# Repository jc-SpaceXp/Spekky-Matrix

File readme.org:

** Spekky Matrix
A FreeRTOS based project were a spectrum analyser is displayed on a LED matrix board run from a STM32 device
*** Detailed Description
A series of cascaded STP16CP05 LED IC drivers forms a 8x32 SMD (0603 Imperial)
LED matrix. This LED matrix then displays the fast fourier transform (FFT) of
an incoming audio signal picked up by a I2S digital microphone. The incoming
audio is a double buffered DMA signal. The LED matrix is driven via the
STM32's SPI interface. All while internal hardware timers and FreeRTOS are
responsible for accurate timing e.g. refresh rate of LED matrix and data
acquisition.

The Manhattan prototype uses a MAX7219 based 8x8 LED matrix breakout board
which was then cascaded to for a 8x32 LED matrix as well. In the PCB version
the STP16CP05 LED IC driver replaces the MAX7219 8x8 LED matrix.
*** Tools
The following tools are needed to build this project
- make
- [[https://developer.arm.com/downloads/-/gnu-rm][arm-none-eabi-gcc]]
- [[https://gcc.gnu.org/][gcc]] (for unit tests)
- [[https://github.com/stlink-org/stlink][st-flash]] in order to interact with the STM32
*** Progress / Milestones
- [X] Create LED matrix driver for MAX7219 devices
- [X] Drive LED matrix from STM32 using FreeRTOS
- [X] Run FFT off target
- [X] Verify FFT on target (using off target results as a guide)
- [X] Verify that LED matrix can be driven alongside FFT code (manually verified, no delays etc.)
- [X] Capture data from mic
- [X] Verify output of mic from raw logic analyser data (using SigPlotI2S)
- [X] Capture data from mic via DMA
- [X] Perform FFT on this raw logic analyser data with a sine wave test tone (off-target)
- [X] Animate FFT graphs to get a rough estimate of how the LED matrix will display it (off-target)
- [X] Perform FFT on mic data sampled by STM32 with a sine wave test tone (off-target)
- [X] Verify that LED matrix can be driven along with data capture and processing
- [X] Perform FFT on captured mic data to drive LED matrix
- [X] Adapt project to PCB
*** I2S Mic FFT Data Visualised
**** Logic Analyser Data (Sine 1kHz Test Tone)
FFT size = 64, start offset = 0, next offset = 32, FPS = 4

[[file:media/python_fft_logic_analyser_sine_1k.gif]]
**** Spekky Matrix Calculations
FFT size = 64, bin resolution = (1/60E-6)/64 --> ~260Hz

Note: I measured one Ws period as 60us on PulseView hence the 1/60E-6 above
***** 8x32 LED Matrix (Sine 2kHz Test Tone)
Peak expected at the 7th/8th bin (2000 / 260 = ~7.69)

[[file:media/blackman_harris_sine_2k.gif]]
***** 8x32 LED Matrix (Sine 4kHz Test Tone)
Peak expected at the 15th/16th bin (4000 / 260 = ~15.36)

[[file:media/blackman_harris_sine_4k.gif]]
***** 8x32 LED Matrix (Sine Sweep Test)
Since the I2S Ws period is 60us, this gives us a sampling frequency of 16.66 kHz.
 Giving us a visual representation of 0-8.88 kHz with Spekky Matrix

[[https://www.youtube.com/watch?v=dU80Fagdy28][Sine sweep source (youtube link)]]

Note: Gif is played at 2.5x speed, see mp4 for realtime playback and audio of sweep test

[[file:media/blackman_harris_sine_sweep.gif]]
*** Schematic
[[file:schematic_v26.pdf]]
*** KiCad PCB
**** BOM
[[file:pcb/kicad/spekky_matrix_bom.csv]]
**** 3D Renders
[[file:pcb/kicad/pcb_3d_front.png]]
[[file:pcb/kicad/pcb_3d_back.png]]
**** PCB v01 Test Patterns
Only displaying test patterns on PCB as v01 has the I2S footprint in the wrong orientation.

Attempted fix hasn't worked, PCB revision v04 contains fixed I2S footprint and test points.
[[file:media/pcb_v01_test_pattern_01.jpg]]
[[file:media/pcb_v01_test_pattern_02.jpg]]
*** Execution Timeline
Rough timing of how long each task/sub-task takes to complete

Actual times are a mean of the traces from the timing branch
[[file:execution_timeline.jpg]]
*** Submodules
- [[https://www.freertos.org/][FreeRTOS]]
- [[https://www.arm.com/technologies/cmsis][CMSIS V6]]
- [[https://github.com/ARM-software/CMSIS-DSP][ARM CMSIS DSP]]
- [[https://github.com/STMicroelectronics/stm32g4xx-nucleo-bsp][STM32G4xx Nucleo BSP]]
- [[https://github.com/STMicroelectronics/stm32g4xx_hal_driver][STM32G4 HAL]]
- [[https://github.com/STMicroelectronics/cmsis_device_g4][CMSIS G4]] CMSIS device library
- [[https://github.com/silentbicycle/greatest][Greatest]] C test framework
- [[https://github.com/meekrosoft/fff][fff]] C test doubles
- [[https://github.com/lucasssvaz/SigPlotI2S][SigPlotI2S]] Plot I2S PulseView/Sigrok output data

CMSIS will also produce linker warnings due to newlib e.g. "_write is not
implemented and will always fail". There is quite a bit of a size overhead
when pulling in all the CMSIS modules. An average project would be
around ~100Mb. This increases with FreeRTOS too.

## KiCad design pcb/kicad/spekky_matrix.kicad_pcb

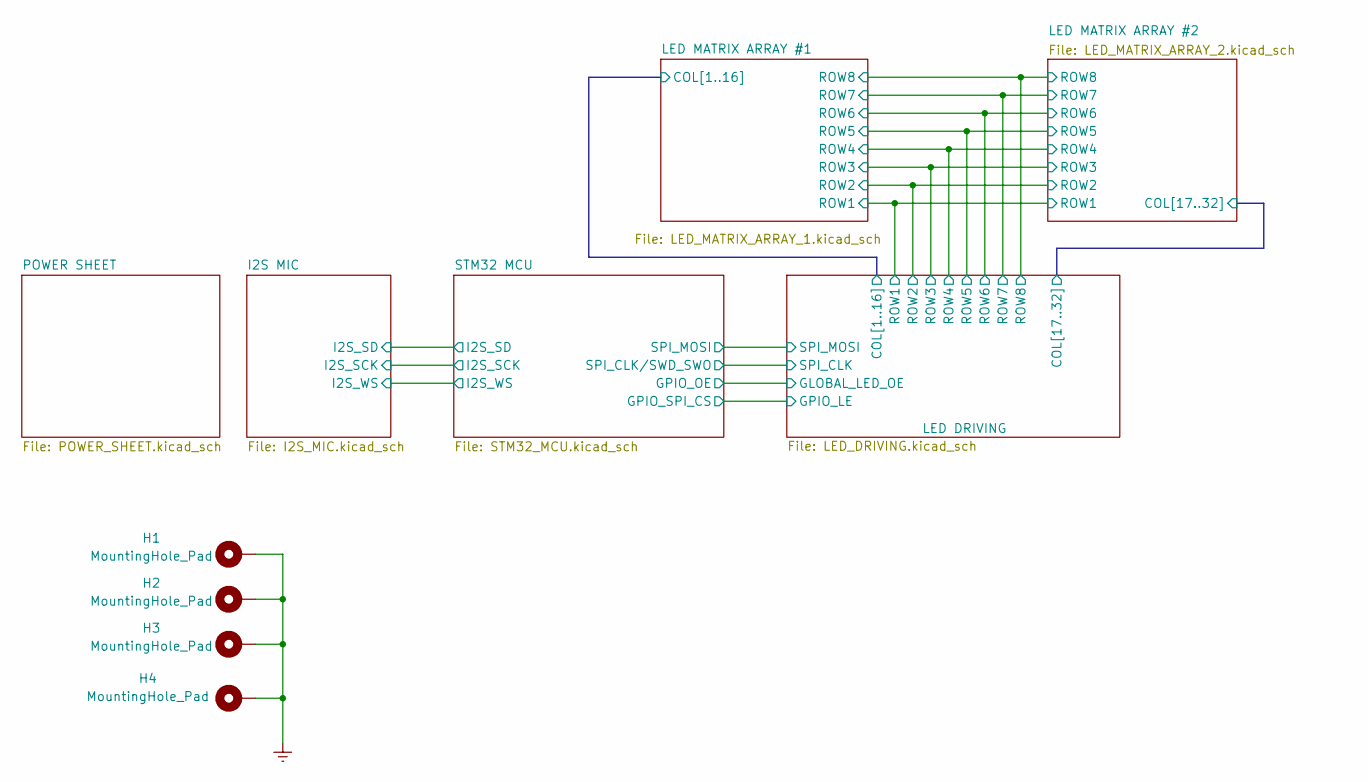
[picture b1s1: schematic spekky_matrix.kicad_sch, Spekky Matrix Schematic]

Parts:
H1, H2, H3, H4: MountingHole_Pad; MountingHole_3.2mm_M3_Pad

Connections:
GND: H1.1, H2.1, H3.1, H4.1; also elsewhere on the board

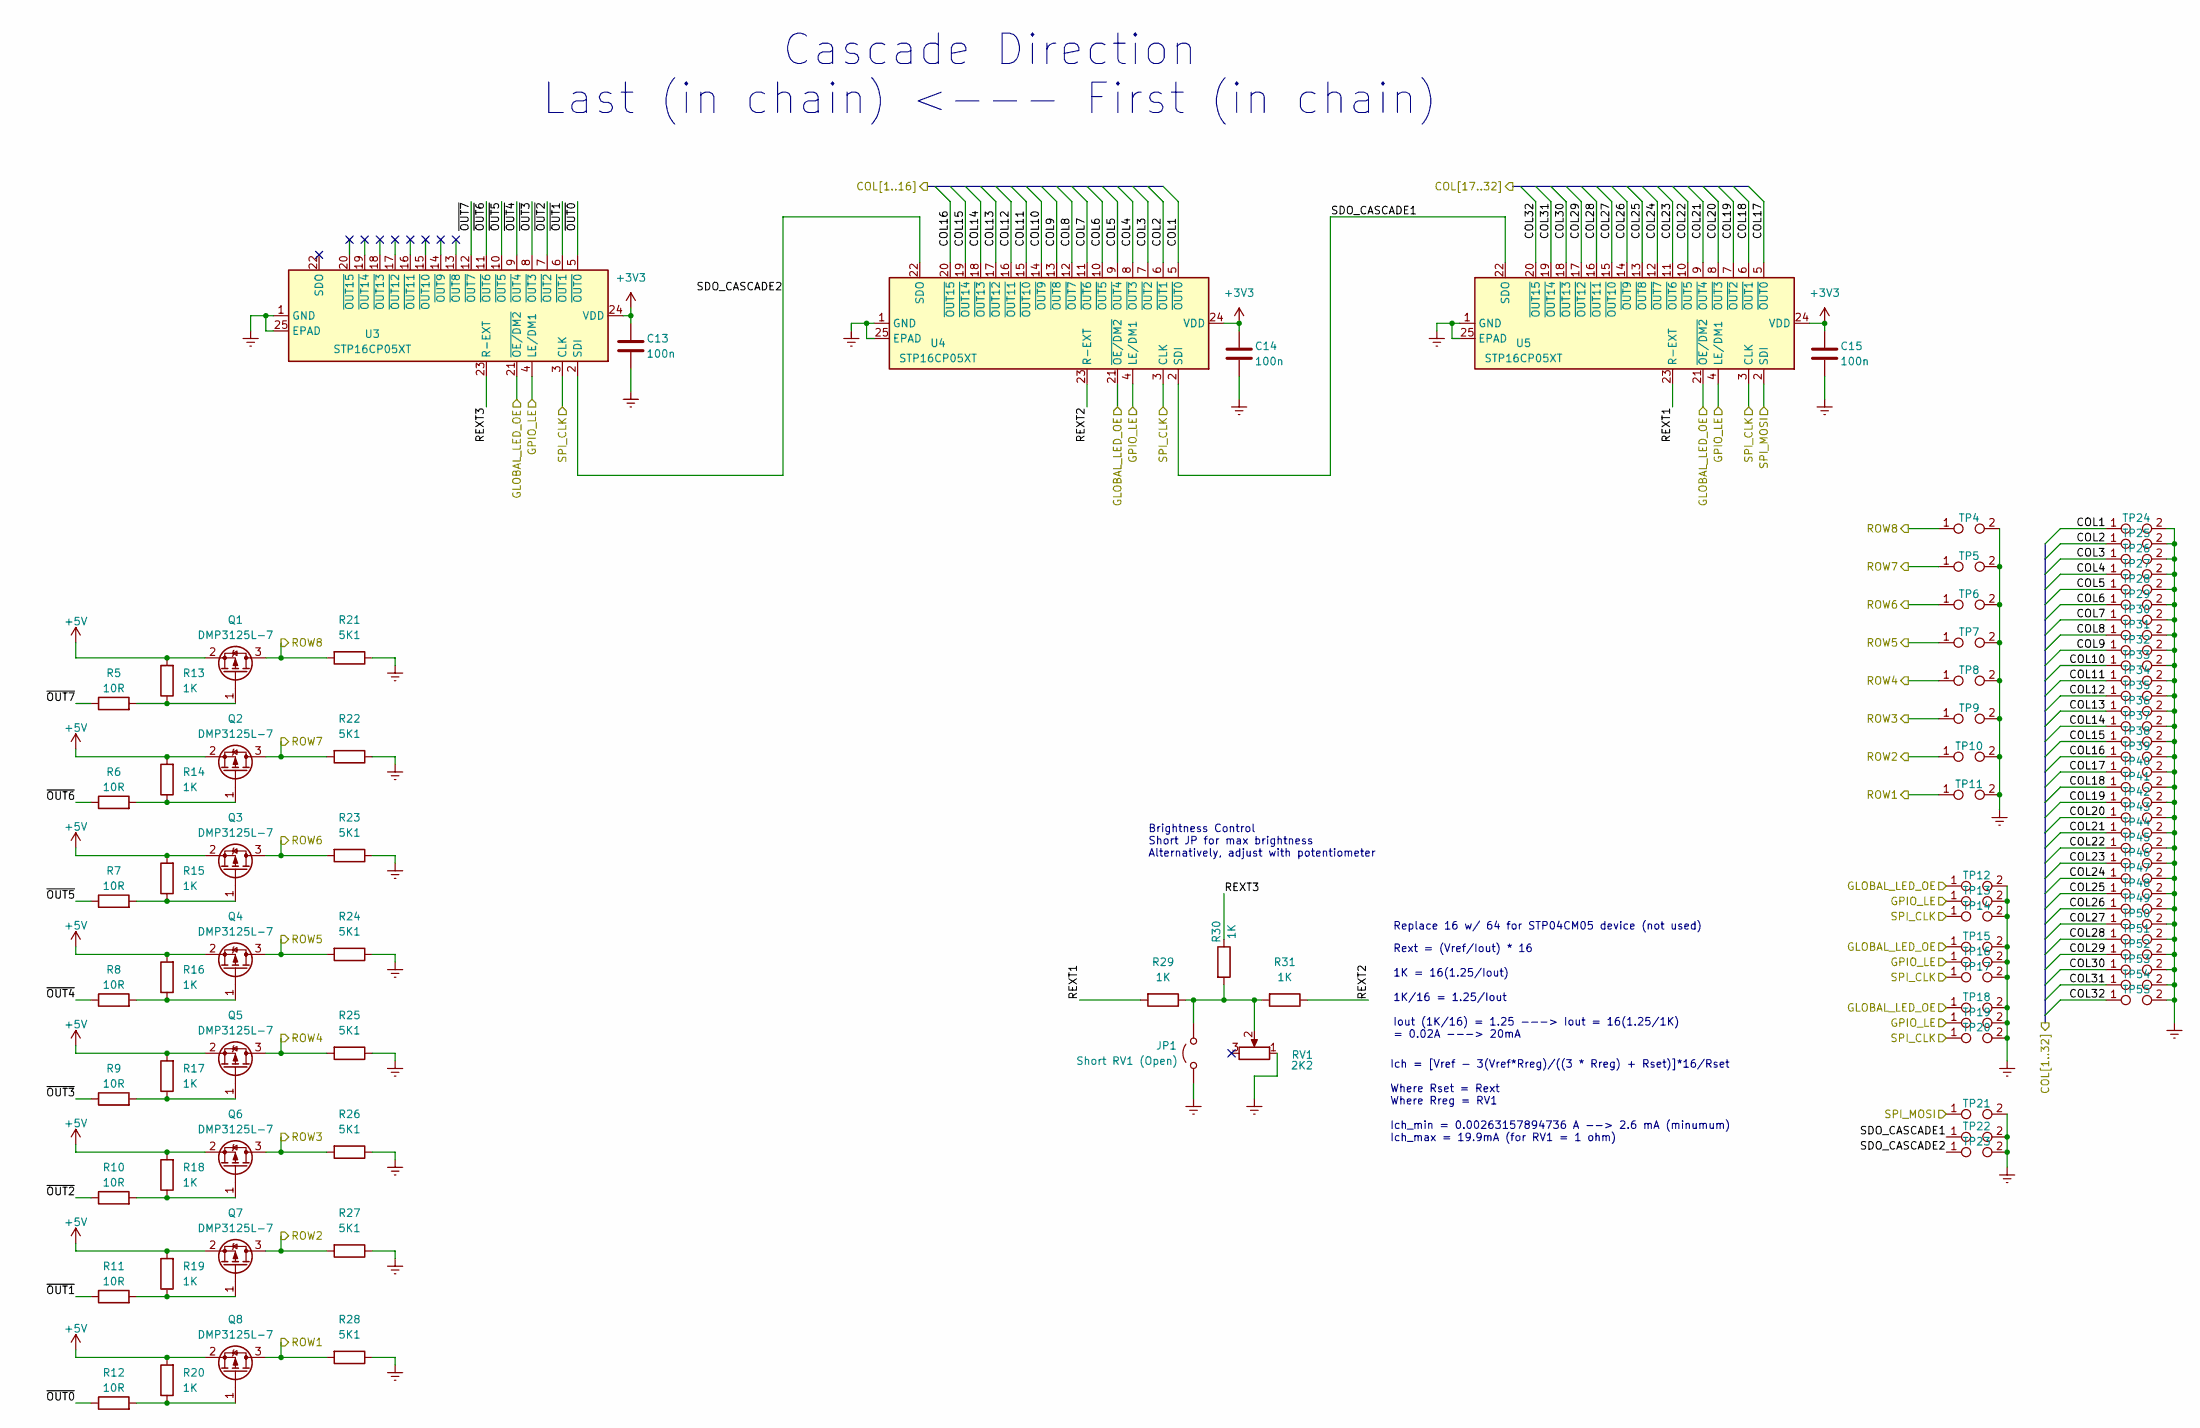
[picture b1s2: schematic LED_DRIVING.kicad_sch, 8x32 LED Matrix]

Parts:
C13, C14, C15: 100n; C_0603_1608Metric; MPN C0603C104J3RACTU
JP1: Short RV1 (Open); PinHeader_1x02_P2.54mm_Vertical
Q1, Q2, Q3, Q4, Q5, Q6, Q7, Q8: DMP3125L-7; SOT-23; MPN DMP3125L-7
R5, R6, R7, R8, R9, R10, R11, R12: 10R; R_0603_1608Metric; MPN RT0603FRE0710RL
R13, R14, R15, R16, R17, R18, R19, R20, R29, R30, R31: 1K; R_0603_1608Metric; MPN RT0603DRE071KL
R21, R22, R23, R24, R25, R26, R27, R28: 5K1; R_0603_1608Metric; MPN RT0603FRE075K1L
RV1: 2K2; Potentiometer_Bourns_3386F_Vertical; MPN 3386F-1-222LF
TP4, TP5, TP11, TP16, TP24, TP25, TP26, TP27, TP28, TP29, TP30, TP31, TP32, TP33, TP34, TP35, TP36, TP37, TP38, TP39, TP40, TP41, TP42, TP43, TP44, TP45, TP46, TP47, TP48, TP49, TP50, TP51, TP52, TP53, TP54, TP55: TestPoint_2Pole; D_0805_2012Metric
TP6, TP7, TP8, TP9, TP10, TP12, TP13, TP14, TP15, TP17, TP18, TP19, TP20, TP21, TP22, TP23: TestPoint_2Pole; D_MicroMELF
U3, U4, U5: STP16CP05XT; HTSSOP-24-1EP_4.4x7.8mm_P0.65mm_EP3.2x5mm; MPN STP16CP05XTTR

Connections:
+3V3: C13.1, C14.1, C15.1, U3.24 (VDD), U4.24 (VDD), U5.24 (VDD); also elsewhere on the board
+5V: Q1.2 (S), Q2.2 (S), Q3.2 (S), Q4.2 (S), Q5.2 (S), Q6.2 (S), Q7.2 (S), Q8.2 (S), R13.2, R14.2, R15.2, R16.2, R17.2, R18.2, R19.2, R20.2; also elsewhere on the board
/LED DRIVING/COL1: TP24.1, U4.5 (~OUT0); also elsewhere on the board
/LED DRIVING/COL2: TP25.1, U4.6 (~OUT1); also elsewhere on the board
/LED DRIVING/COL3: TP26.1, U4.7 (~OUT2); also elsewhere on the board
/LED DRIVING/COL4: TP27.1, U4.8 (~OUT3); also elsewhere on the board
/LED DRIVING/COL5: TP28.1, U4.9 (~OUT4); also elsewhere on the board
/LED DRIVING/COL6: TP29.1, U4.10 (~OUT5); also elsewhere on the board
/LED DRIVING/COL7: TP30.1, U4.11 (~OUT6); also elsewhere on the board
/LED DRIVING/COL8: TP31.1, U4.12 (~OUT7); also elsewhere on the board
/LED DRIVING/COL9: TP32.1, U4.13 (~OUT8); also elsewhere on the board
/LED DRIVING/COL10: TP33.1, U4.14 (~OUT9); also elsewhere on the board
/LED DRIVING/COL11: TP34.1, U4.15 (~OUT10); also elsewhere on the board
/LED DRIVING/COL12: TP35.1, U4.16 (~OUT11); also elsewhere on the board
/LED DRIVING/COL13: TP36.1, U4.17 (~OUT12); also elsewhere on the board
/LED DRIVING/COL14: TP37.1, U4.18 (~OUT13); also elsewhere on the board
/LED DRIVING/COL15: TP38.1, U4.19 (~OUT14); also elsewhere on the board
/LED DRIVING/COL16: TP39.1, U4.20 (~OUT15); also elsewhere on the board
/LED DRIVING/COL17: TP40.1, U5.5 (~OUT0); also elsewhere on the board
/LED DRIVING/COL18: TP41.1, U5.6 (~OUT1); also elsewhere on the board
/LED DRIVING/COL19: TP42.1, U5.7 (~OUT2); also elsewhere on the board
/LED DRIVING/COL20: TP43.1, U5.8 (~OUT3); also elsewhere on the board
/LED DRIVING/COL21: TP44.1, U5.9 (~OUT4); also elsewhere on the board
/LED DRIVING/COL22: TP45.1, U5.10 (~OUT5); also elsewhere on the board
/LED DRIVING/COL23: TP46.1, U5.11 (~OUT6); also elsewhere on the board
/LED DRIVING/COL24: TP47.1, U5.12 (~OUT7); also elsewhere on the board
/LED DRIVING/COL25: TP48.1, U5.13 (~OUT8); also elsewhere on the board
/LED DRIVING/COL26: TP49.1, U5.14 (~OUT9); also elsewhere on the board
/LED DRIVING/COL27: TP50.1, U5.15 (~OUT10); also elsewhere on the board
/LED DRIVING/COL28: TP51.1, U5.16 (~OUT11); also elsewhere on the board
/LED DRIVING/COL29: TP52.1, U5.17 (~OUT12); also elsewhere on the board
/LED DRIVING/COL30: TP53.1, U5.18 (~OUT13); also elsewhere on the board
/LED DRIVING/COL31: TP54.1, U5.19 (~OUT14); also elsewhere on the board
/LED DRIVING/COL32: TP55.1, U5.20 (~OUT15); also elsewhere on the board
/LED DRIVING/GLOBAL_LED_OE: TP12.1, TP15.1, TP18.1, U3.21 (~OE/DM2), U4.21 (~OE/DM2), U5.21 (~OE/DM2); also elsewhere on the board
/LED DRIVING/GPIO_LE: TP13.1, TP16.1, TP19.1, U3.4 (LE/DM1), U4.4 (LE/DM1), U5.4 (LE/DM1); also elsewhere on the board
/LED DRIVING/REXT1: R29.2, U5.23 (R-EXT)
/LED DRIVING/REXT2: R31.1, U4.23 (R-EXT)
/LED DRIVING/REXT3: R30.1, U3.23 (R-EXT)
/LED DRIVING/ROW1: Q8.3 (D), R28.2, TP11.1; also elsewhere on the board
/LED DRIVING/ROW2: Q7.3 (D), R27.2, TP10.1; also elsewhere on the board
/LED DRIVING/ROW3: Q6.3 (D), R26.2, TP9.1; also elsewhere on the board
/LED DRIVING/ROW4: Q5.3 (D), R25.2, TP8.1; also elsewhere on the board
/LED DRIVING/ROW5: Q4.3 (D), R24.2, TP7.1; also elsewhere on the board
/LED DRIVING/ROW6: Q3.3 (D), R23.2, TP6.1; also elsewhere on the board
/LED DRIVING/ROW7: Q2.3 (D), R22.2, TP5.1; also elsewhere on the board
/LED DRIVING/ROW8: Q1.3 (D), R21.2, TP4.1; also elsewhere on the board
/LED DRIVING/SDO_CASCADE1: TP22.1, U4.2 (SDI), U5.22 (SDO)
/LED DRIVING/SDO_CASCADE2: TP23.1, U3.2 (SDI), U4.22 (SDO)
/LED DRIVING/SPI_CLK: TP14.1, TP17.1, TP20.1, U3.3 (CLK), U4.3 (CLK), U5.3 (CLK); also elsewhere on the board
/LED DRIVING/SPI_MOSI: TP21.1, U5.2 (SDI); also elsewhere on the board
/LED DRIVING/~OUT0: R12.1, U3.5 (~OUT0)
/LED DRIVING/~OUT1: R11.1, U3.6 (~OUT1)
/LED DRIVING/~OUT2: R10.1, U3.7 (~OUT2)
/LED DRIVING/~OUT3: R9.1, U3.8 (~OUT3)
/LED DRIVING/~OUT4: R8.1, U3.9 (~OUT4)
/LED DRIVING/~OUT5: R7.1, U3.10 (~OUT5)
/LED DRIVING/~OUT6: R6.1, U3.11 (~OUT6)
/LED DRIVING/~OUT7: R5.1, U3.12 (~OUT7)
GND: C13.2, C14.2, C15.2, JP1.1 (A), R21.1, R22.1, R23.1, R24.1, R25.1, R26.1, R27.1, R28.1, RV1.1, TP4.2, TP5.2, TP6.2, TP7.2, TP8.2, TP9.2, TP10.2, TP11.2, TP12.2, TP13.2, TP14.2, TP15.2, TP16.2, TP17.2, TP18.2, TP19.2, TP20.2, TP21.2, TP22.2, TP23.2, TP24.2, TP25.2, TP26.2, TP27.2, TP28.2, TP29.2, TP30.2, TP31.2, TP32.2, TP33.2, TP34.2, TP35.2, TP36.2, TP37.2, TP38.2, TP39.2, TP40.2, TP41.2, TP42.2, TP43.2, TP44.2, TP45.2, TP46.2, TP47.2, TP48.2, TP49.2, TP50.2, TP51.2, TP52.2, TP53.2, TP54.2, TP55.2, U3.1 (GND), U3.25 (EPAD), U4.1 (GND), U4.25 (EPAD), U5.1 (GND), U5.25 (EPAD); also elsewhere on the board
unnamed: JP1.2 (B), R29.1, R30.2, R31.2, RV1.2
unnamed: Q1.1 (G), R5.2, R13.1
unnamed: Q2.1 (G), R6.2, R14.1
unnamed: Q3.1 (G), R7.2, R15.1
unnamed: Q4.1 (G), R8.2, R16.1
unnamed: Q5.1 (G), R9.2, R17.1
unnamed: Q6.1 (G), R10.2, R18.1
unnamed: Q7.1 (G), R11.2, R19.1
unnamed: Q8.1 (G), R12.2, R20.1

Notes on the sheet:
Rext = (Vref/Iout) * 16 1K = 16(1.25/Iout) 1K/16 = 1.25/Iout Iout (1K/16) = 1.25 ---> Iout = 16(1.25/1K) = 0.02A ---> 20mA
Cascade Direction Last (in chain) <--- First (in chain)
Brightness Control Short JP for max brightness Alternatively, adjust with potentiometer
Ich = [Vref - 3(Vref*Rreg)/((3 * Rreg) + Rset)]*16/Rset Where Rset = Rext Where Rreg = RV1 Ich_min = 0.00263157894736 A --> 2.6 mA (minumum) Ich_max = 19.9mA (for RV1 = 1 ohm)
Replace 16 w/ 64 for STP04CM05 device (not used)

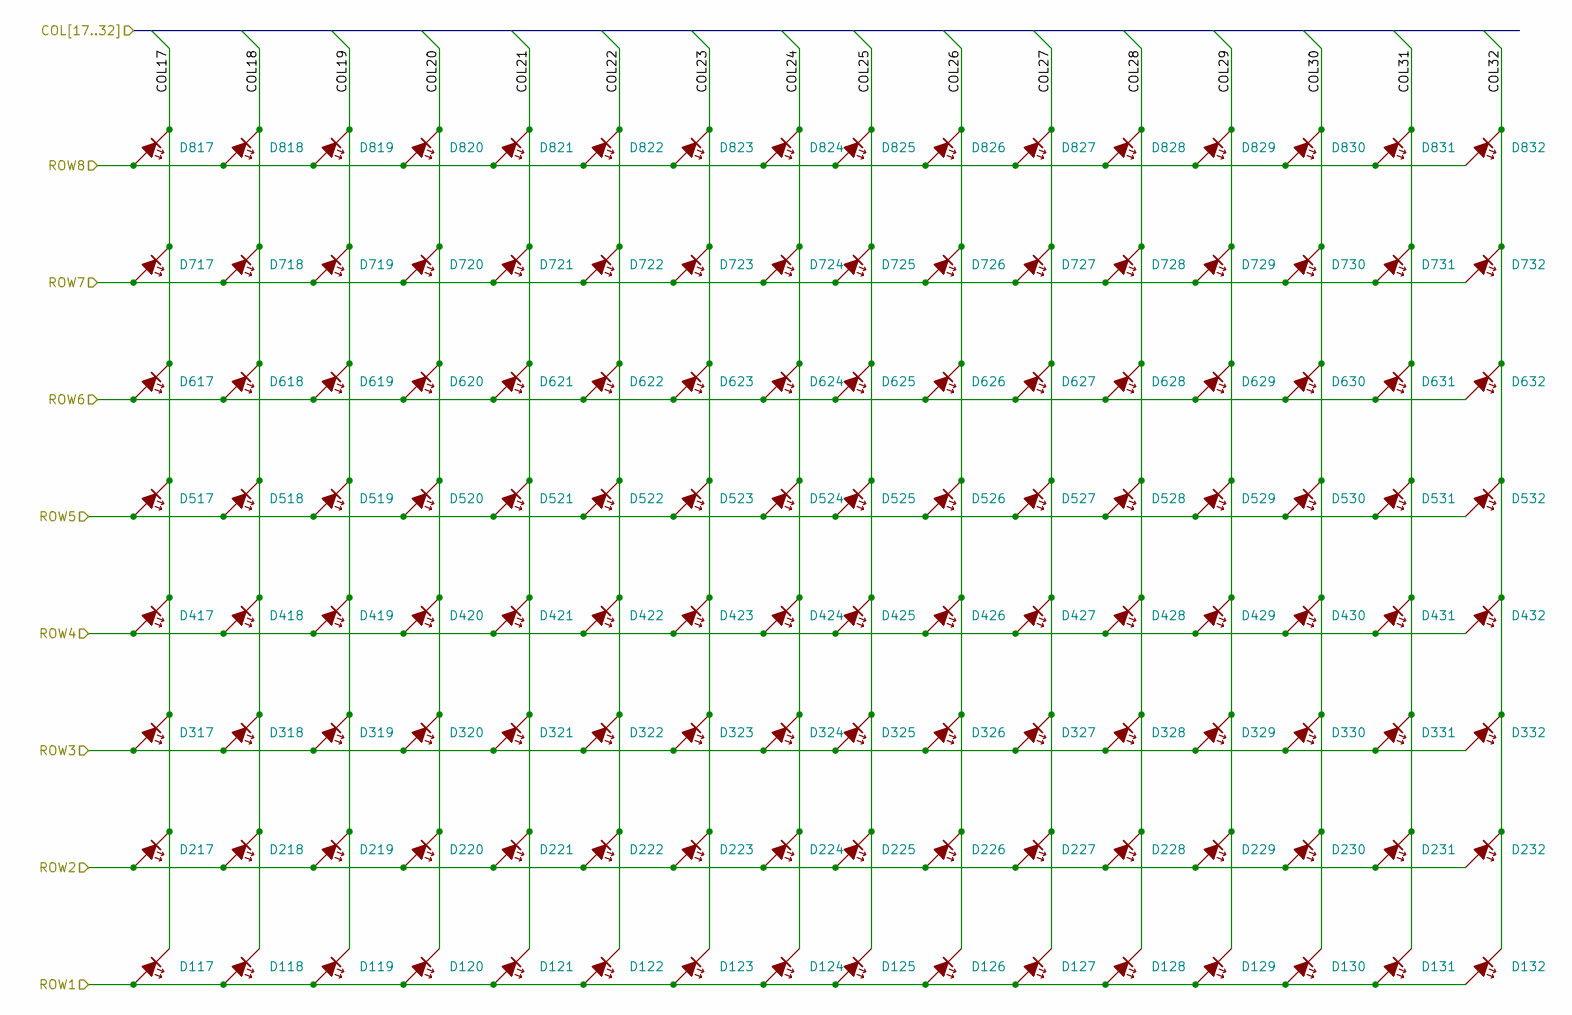
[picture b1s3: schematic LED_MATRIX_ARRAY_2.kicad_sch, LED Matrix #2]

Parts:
D117, D118, D119, D120, D121, D122, D123, D124, D125, D126, D127, D128, D129, D130, D131, D132, D217, D218, D219, D220, D221, D222, D223, D224, D225, D226, D227, D228, D229, D230, D231, D232, D317, D318, D319, D320, D321, D322, D323, D324, D325, D326, D327, D328, D329, D330, D331, D332, D417, D418, D419, D420, D421, D422, D423, D424, D425, D426, D427, D428, D429, D430, D431, D432, D517, D518, D519, D520, D521, D522, D523, D524, D525, D526, D527, D528, D529, D530, D531, D532, D617, D618, D619, D620, D621, D622, D623, D624, D625, D626, D627, D628, D629, D630, D631, D632, D717, D718, D719, D720, D721, D722, D723, D724, D725, D726, D727, D728, D729, D730, D731, D732, D817, D818, D819, D820, D821, D822, D823, D824, D825, D826, D827, D828, D829, D830, D831, D832: LED Matrix (RED); LED_0603_1608Metric_Pad1.05x0.95mm_HandSolder; MPN LTST-C190KRKT

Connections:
/LED DRIVING/COL17: D117.1 (K), D217.1 (K), D317.1 (K), D417.1 (K), D517.1 (K), D617.1 (K), D717.1 (K), D817.1 (K); also elsewhere on the board
/LED DRIVING/COL18: D118.1 (K), D218.1 (K), D318.1 (K), D418.1 (K), D518.1 (K), D618.1 (K), D718.1 (K), D818.1 (K); also elsewhere on the board
/LED DRIVING/COL19: D119.1 (K), D219.1 (K), D319.1 (K), D419.1 (K), D519.1 (K), D619.1 (K), D719.1 (K), D819.1 (K); also elsewhere on the board
/LED DRIVING/COL20: D120.1 (K), D220.1 (K), D320.1 (K), D420.1 (K), D520.1 (K), D620.1 (K), D720.1 (K), D820.1 (K); also elsewhere on the board
/LED DRIVING/COL21: D121.1 (K), D221.1 (K), D321.1 (K), D421.1 (K), D521.1 (K), D621.1 (K), D721.1 (K), D821.1 (K); also elsewhere on the board
/LED DRIVING/COL22: D122.1 (K), D222.1 (K), D322.1 (K), D422.1 (K), D522.1 (K), D622.1 (K), D722.1 (K), D822.1 (K); also elsewhere on the board
/LED DRIVING/COL23: D123.1 (K), D223.1 (K), D323.1 (K), D423.1 (K), D523.1 (K), D623.1 (K), D723.1 (K), D823.1 (K); also elsewhere on the board
/LED DRIVING/COL24: D124.1 (K), D224.1 (K), D324.1 (K), D424.1 (K), D524.1 (K), D624.1 (K), D724.1 (K), D824.1 (K); also elsewhere on the board
/LED DRIVING/COL25: D125.1 (K), D225.1 (K), D325.1 (K), D425.1 (K), D525.1 (K), D625.1 (K), D725.1 (K), D825.1 (K); also elsewhere on the board
/LED DRIVING/COL26: D126.1 (K), D226.1 (K), D326.1 (K), D426.1 (K), D526.1 (K), D626.1 (K), D726.1 (K), D826.1 (K); also elsewhere on the board
/LED DRIVING/COL27: D127.1 (K), D227.1 (K), D327.1 (K), D427.1 (K), D527.1 (K), D627.1 (K), D727.1 (K), D827.1 (K); also elsewhere on the board
/LED DRIVING/COL28: D128.1 (K), D228.1 (K), D328.1 (K), D428.1 (K), D528.1 (K), D628.1 (K), D728.1 (K), D828.1 (K); also elsewhere on the board
/LED DRIVING/COL29: D129.1 (K), D229.1 (K), D329.1 (K), D429.1 (K), D529.1 (K), D629.1 (K), D729.1 (K), D829.1 (K); also elsewhere on the board
/LED DRIVING/COL30: D130.1 (K), D230.1 (K), D330.1 (K), D430.1 (K), D530.1 (K), D630.1 (K), D730.1 (K), D830.1 (K); also elsewhere on the board
/LED DRIVING/COL31: D131.1 (K), D231.1 (K), D331.1 (K), D431.1 (K), D531.1 (K), D631.1 (K), D731.1 (K), D831.1 (K); also elsewhere on the board
/LED DRIVING/COL32: D132.1 (K), D232.1 (K), D332.1 (K), D432.1 (K), D532.1 (K), D632.1 (K), D732.1 (K), D832.1 (K); also elsewhere on the board
/LED DRIVING/ROW1: D117.2 (A), D118.2 (A), D119.2 (A), D120.2 (A), D121.2 (A), D122.2 (A), D123.2 (A), D124.2 (A), D125.2 (A), D126.2 (A), D127.2 (A), D128.2 (A), D129.2 (A), D130.2 (A), D131.2 (A), D132.2 (A); also elsewhere on the board
/LED DRIVING/ROW2: D217.2 (A), D218.2 (A), D219.2 (A), D220.2 (A), D221.2 (A), D222.2 (A), D223.2 (A), D224.2 (A), D225.2 (A), D226.2 (A), D227.2 (A), D228.2 (A), D229.2 (A), D230.2 (A), D231.2 (A), D232.2 (A); also elsewhere on the board
/LED DRIVING/ROW3: D317.2 (A), D318.2 (A), D319.2 (A), D320.2 (A), D321.2 (A), D322.2 (A), D323.2 (A), D324.2 (A), D325.2 (A), D326.2 (A), D327.2 (A), D328.2 (A), D329.2 (A), D330.2 (A), D331.2 (A), D332.2 (A); also elsewhere on the board
/LED DRIVING/ROW4: D417.2 (A), D418.2 (A), D419.2 (A), D420.2 (A), D421.2 (A), D422.2 (A), D423.2 (A), D424.2 (A), D425.2 (A), D426.2 (A), D427.2 (A), D428.2 (A), D429.2 (A), D430.2 (A), D431.2 (A), D432.2 (A); also elsewhere on the board
/LED DRIVING/ROW5: D517.2 (A), D518.2 (A), D519.2 (A), D520.2 (A), D521.2 (A), D522.2 (A), D523.2 (A), D524.2 (A), D525.2 (A), D526.2 (A), D527.2 (A), D528.2 (A), D529.2 (A), D530.2 (A), D531.2 (A), D532.2 (A); also elsewhere on the board
/LED DRIVING/ROW6: D617.2 (A), D618.2 (A), D619.2 (A), D620.2 (A), D621.2 (A), D622.2 (A), D623.2 (A), D624.2 (A), D625.2 (A), D626.2 (A), D627.2 (A), D628.2 (A), D629.2 (A), D630.2 (A), D631.2 (A), D632.2 (A); also elsewhere on the board
/LED DRIVING/ROW7: D717.2 (A), D718.2 (A), D719.2 (A), D720.2 (A), D721.2 (A), D722.2 (A), D723.2 (A), D724.2 (A), D725.2 (A), D726.2 (A), D727.2 (A), D728.2 (A), D729.2 (A), D730.2 (A), D731.2 (A), D732.2 (A); also elsewhere on the board
/LED DRIVING/ROW8: D817.2 (A), D818.2 (A), D819.2 (A), D820.2 (A), D821.2 (A), D822.2 (A), D823.2 (A), D824.2 (A), D825.2 (A), D826.2 (A), D827.2 (A), D828.2 (A), D829.2 (A), D830.2 (A), D831.2 (A), D832.2 (A); also elsewhere on the board

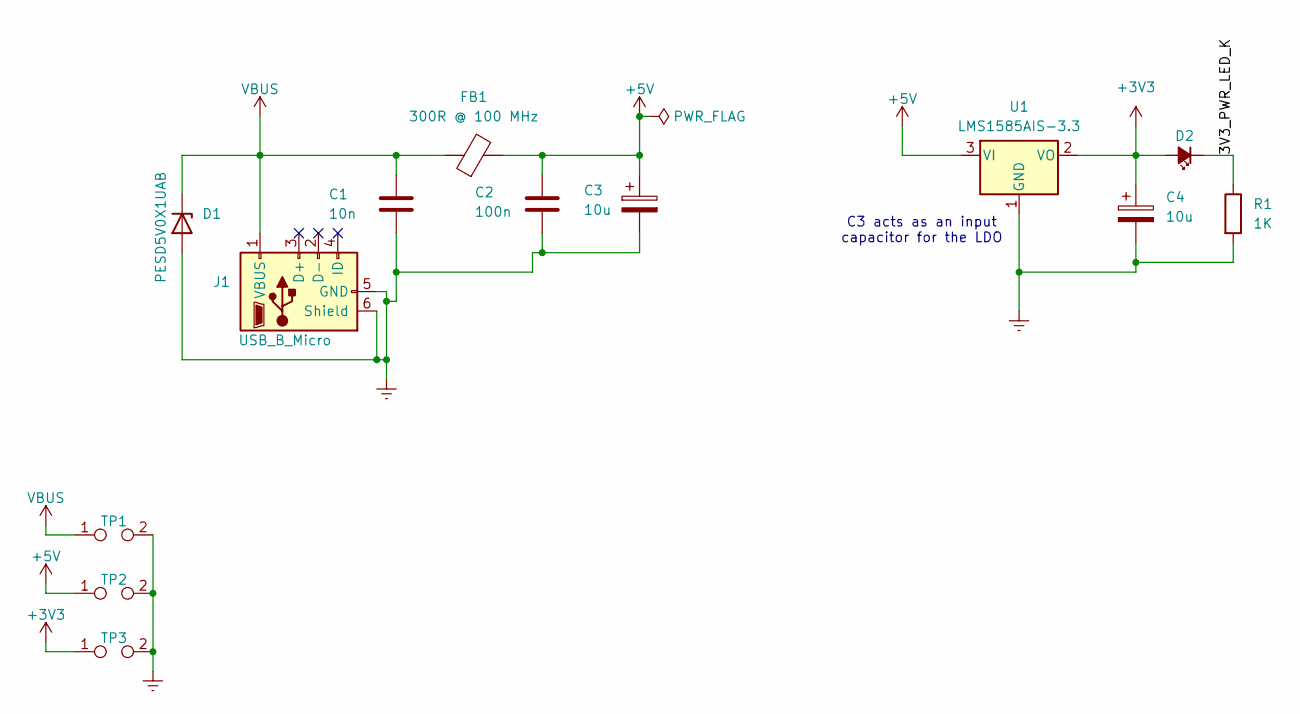
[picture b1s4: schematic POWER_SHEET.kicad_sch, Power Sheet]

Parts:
C1: 10n; C_0603_1608Metric; MPN GCM188R71H103KA37J
C2: 100n; C_0603_1608Metric; MPN C0603C104J3RACTU
C3, C4: 10u; CP_Elec_4x4.5; MPN EDH106M016A9BAA
D1: PESD5V0X1UAB; D_SOD-523; MPN PESD5V0X1UAB,115
D2: 3V3 LED (RED); LED_0603_1608Metric_Pad1.05x0.95mm_HandSolder; MPN LTST-C190KRKT
FB1: 300R @ 100 MHz; L_0603_1608Metric; MPN HI2220R301R-10
J1: USB_B_Micro; USB_Micro-B_Amphenol_10118194-0001LF_Horizontal; MPN 10118194-0001LF
R1: 1K; R_0603_1608Metric; MPN RT0603DRE071KL
TP1, TP3: TestPoint_2Pole; D_MicroMELF
TP2: TestPoint_2Pole; D_0805_2012Metric
U1: LMS1585AIS-3.3; TO-263-3_TabPin2; MPN LMS1585AIS-3.3/NOPB

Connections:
+3V3: C4.1, D2.2 (A), TP3.1, U1.2 (VO); also elsewhere on the board
+5V: C2.1, C3.1, FB1.2, TP2.1, U1.3 (VI); also elsewhere on the board
/POWER SHEET/3V3_PWR_LED_K: D2.1 (K), R1.1
GND: C1.2, C2.2, C3.2, C4.2, D1.2 (A), J1.5 (GND), J1.6 (Shield), R1.2, TP1.2, TP2.2, TP3.2, U1.1 (GND); also elsewhere on the board
VBUS: C1.1, D1.1 (K), FB1.1, J1.1 (VBUS), TP1.1

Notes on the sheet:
C3 acts as an input capacitor for the LDO

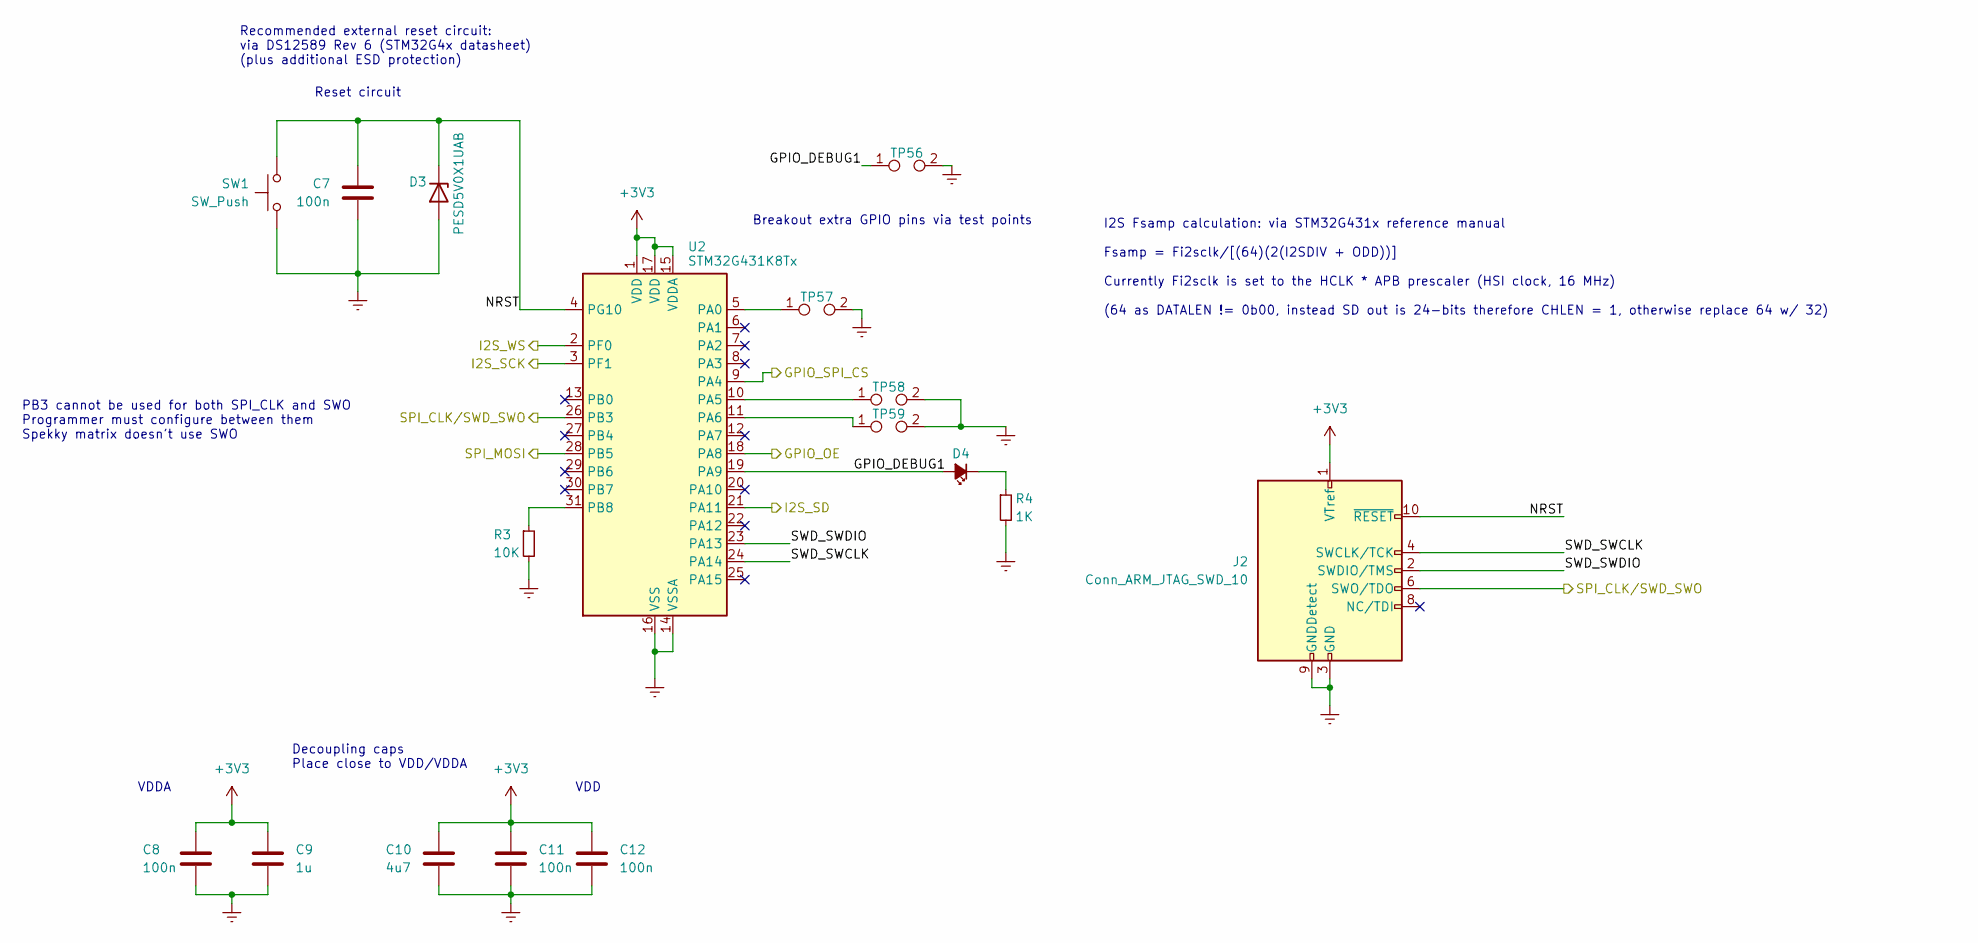
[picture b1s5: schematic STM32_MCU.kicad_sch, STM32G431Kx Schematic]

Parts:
C7, C8, C11, C12: 100n; C_0603_1608Metric; MPN C0603C104J3RACTU
C9: 1u; C_0603_1608Metric; MPN GCG188L8EE105KA07D
C10: 4u7; C_0603_1608Metric; MPN GRM188Z71C475KE21D
D3: PESD5V0X1UAB; D_SOD-523; MPN PESD5V0X1UAB,115
D4: GPIO Debug LED (GREEN); LED_0603_1608Metric_Pad1.05x0.95mm_HandSolder; MPN LTST-C190KGKT
J2: Conn_ARM_JTAG_SWD_10; PinHeader_2x05_P1.27mm_Vertical; MPN FTSH-105-01-L-D-K
R3: 10K; R_0603_1608Metric; MPN RT0603FRE0710KL
R4: 1K; R_0603_1608Metric; MPN RT0603DRE071KL
SW1: SW_Push; SW_SPST_TL3305A; MPN TL3305AF260QG
TP56, TP57, TP58, TP59: TestPoint_2Pole; D_0402_1005Metric
U2: STM32G431K8Tx; LQFP-32_7x7mm_P0.8mm; MPN STM32G431K8T6

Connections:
+3V3: C8.1, C9.1, C10.1, C11.1, C12.1, J2.1 (VTref), U2.1 (VDD), U2.15 (VDDA), U2.17 (VDD); also elsewhere on the board
/I2S MIC/I2S_SCK: U2.3 (PF1); also elsewhere on the board
/I2S MIC/I2S_SD: U2.21 (PA11); also elsewhere on the board
/I2S MIC/I2S_WS: U2.2 (PF0); also elsewhere on the board
/LED DRIVING/GLOBAL_LED_OE: U2.18 (PA8); also elsewhere on the board
/LED DRIVING/GPIO_LE: U2.9 (PA4); also elsewhere on the board
/LED DRIVING/SPI_CLK: J2.6 (SWO/TDO), U2.26 (PB3); also elsewhere on the board
/LED DRIVING/SPI_MOSI: U2.28 (PB5); also elsewhere on the board
/STM32 MCU/GPIO_DEBUG1: D4.2 (A), TP56.1, U2.19 (PA9)
/STM32 MCU/NRST: C7.2, D3.1 (K), J2.10 (~RESET), SW1.2, U2.4 (PG10)
/STM32 MCU/SWD_SWCLK: J2.4 (SWCLK/TCK), U2.24 (PA14)
/STM32 MCU/SWD_SWDIO: J2.2 (SWDIO/TMS), U2.23 (PA13)
GND: C7.1, C8.2, C9.2, C10.2, C11.2, C12.2, D3.2 (A), J2.3 (GND), J2.5 (GND), J2.9 (GNDDetect), R3.2, R4.2, SW1.1, TP56.2, TP57.2, TP58.2, TP59.2, U2.14 (VSSA), U2.16 (VSS), U2.32 (VSS); also elsewhere on the board
unnamed: D4.1 (K), R4.1
unnamed: TP57.1, U2.5 (PA0)
unnamed: TP58.1, U2.10 (PA5)
unnamed: TP59.1, U2.11 (PA6)
unnamed: R3.1, U2.31 (PB8)

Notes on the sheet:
Decoupling caps Place close to VDD/VDDA
PB3 cannot be used for both SPI_CLK and SWO Programmer must configure between them Spekky matrix doesn't use SWO
Breakout extra GPIO pins via test points
VDD
Recommended external reset circuit: via DS12589 Rev 6 (STM32G4x datasheet) (plus additional ESD protection)
Reset circuit
I2S Fsamp calculation: via STM32G431x reference manual Fsamp = Fi2sclk/[(64)(2(I2SDIV + ODD))] Currently Fi2sclk is set to the HCLK * APB prescaler (HSI clock, 16 MHz) (64 as DATALEN != 0b00, instead SD out is 24-bits therefore CHLEN = 1, otherwise replace 64 w/ 32)
VDDA
